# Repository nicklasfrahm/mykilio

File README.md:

# Mykilio

⚠️ **Experimental**: This repository is under active development. Usage in production is not advised, but any kind of feedback is welcome.

Mykilio is the proposal for a new Living Standard with the goal to reimagine infrastructure management and monitoring. It aims to be scalable, lightweight, extensible and secure by applying IoT principles to the datacenter and homelabs.

## 📖 Documentation

The documentation can be found at https://mykil.io.

## 📊 Statistics

Here are some statistics to document my learnings throughout the development process.

| 💣 Fault         | 📈 Occurrences | 😅 Poor excuse                                                                                          |
| ---------------- | -------------- | ------------------------------------------------------------------------------------------------------- |
| Reverse polarity | 1              | Maybe purple and dark grey were not the best choice for +24V and GND.                                   |
| Overvoltage      | 1              | I have shaky hands and why does everything have to be so small?!                                        |
| Short-circuit    | 1              | Next time I am going to solder proper connectors. Promise!                                              |
| Wrong footprint  | 2              | Why do TQFP and DIP have a different pin numbering!?<br/>It was late and SS/TR is very close to RT/CLK. |

## 📄 License

This project is licensed under the terms of the [MIT license](./LICENSE.md).

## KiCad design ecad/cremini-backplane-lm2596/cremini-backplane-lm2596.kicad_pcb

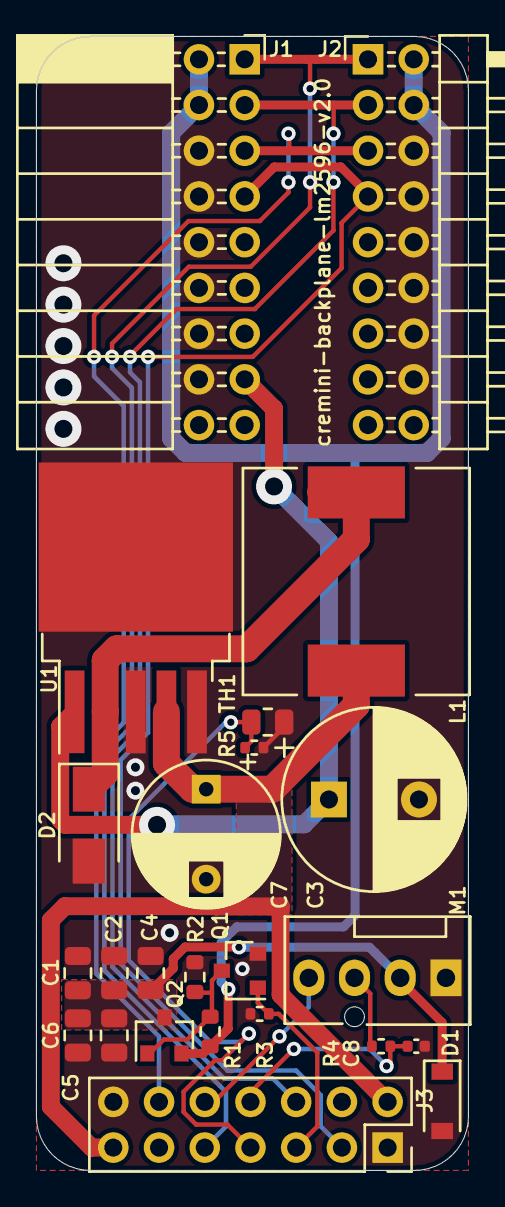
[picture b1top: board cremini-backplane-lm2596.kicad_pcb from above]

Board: 2 copper layers, 24.0 x 63.0 mm, 24 parts (0 on the bottom side), 16 nets.

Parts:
C1, C2, C4, C5, C6: 22uF; C_0805_2012Metric
C3: 680uF; CP_Radial_D10.0mm_P5.00mm
C7: 330uF; CP_Radial_D8.0mm_P5.00mm
C8: 6.8nF; C_0402_1005Metric
D1: B5819W; D_SOD-123
D2: SS54; D_SMA
J1: BUSOUT; PinSocket_2x09_P2.54mm_Horizontal
J2: BUSIN; PinHeader_2x09_P2.54mm_Horizontal
J3: BACKPLANE; PinSocket_2x07_P2.54mm_Vertical
L1: 47uH; L_12x12mm_H8mm
M1: KK 254; FanPinHeader_1x04_P2.54mm_Vertical
Q1: AO3400A; SOT-23
Q2: SI2301CDS-T1-GE3; SOT-23
R1: 1k; R_0603_1608Metric
R2: 1.8k; R_0603_1608Metric
R3, R4, R5: 10k; R_0402_1005Metric
TH1: CMFB103F3950FANT; R_0805_2012Metric
U1: LM2596S-5; TO-263-5_TabPin3

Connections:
5VPSU: C7.1, J3.2, J3.13, L1.2, U1.4
+12V: J1.2, J1.4, J2.2, J2.4, Q2.2, R1.1
FANDCC: J3.5, Q1.1, R3.1
FANFDB: C8.1, J3.8, R4.2
FANPWM: J3.10, M1.4
GND: C1.1, C2.1, C3.2, C4.1, C5.1, C6.1, C7.2, C8.2, D1.2, D2.2, J1.6, J1.8, J1.10, J1.12, J1.14, J1.16, J2.6, J2.8, J2.10, J2.12, J2.14, J2.16, J3.1, J3.14, M1.1, Q1.2, R2.2, R3.2, R5.2, TH1.1, U1.3, U1.5
unnamed: C1.2, C2.2, C4.2, C5.2, C6.2, D1.1, M1.2, Q2.3
unnamed: D2.1, L1.1, U1.2
unnamed: M1.3, R4.1
unnamed: Q1.3, Q2.1, R1.2, R2.1
POWTMP: J3.7, R5.1, TH1.2
SCL: J1.7, J2.7, J3.3
SDA: J1.5, J2.5, J3.12
SRX: J1.3, J2.3, J3.6
STX: J1.1, J2.1, J3.9
VIN: C3.1, J1.9, J1.11, J1.13, J1.15, J2.9, J2.11, J2.13, J2.15, U1.1

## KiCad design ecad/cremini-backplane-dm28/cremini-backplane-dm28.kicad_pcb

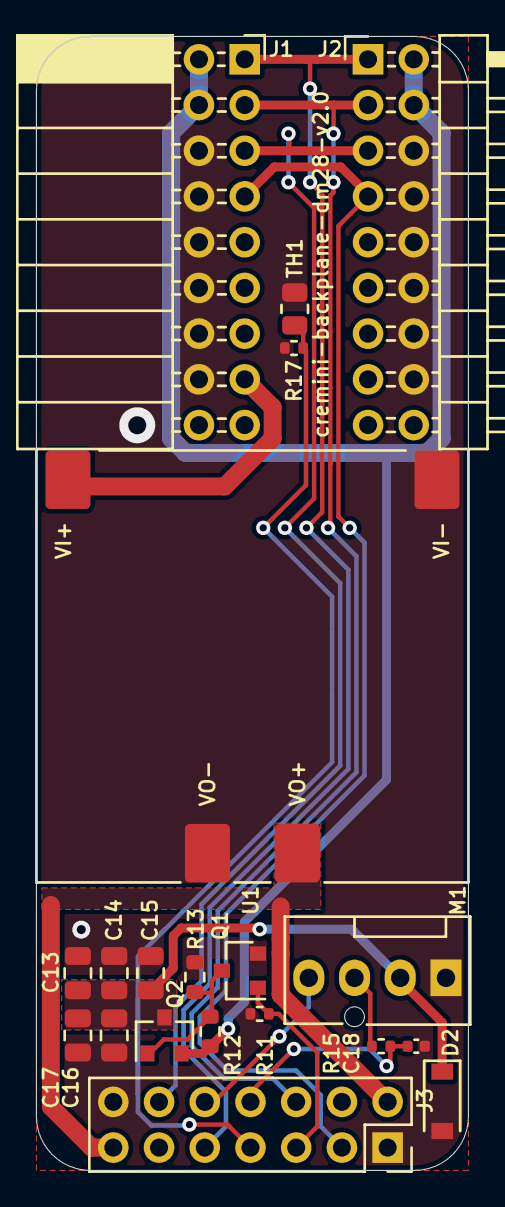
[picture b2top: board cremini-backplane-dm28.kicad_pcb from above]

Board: 2 copper layers, 24.0 x 63.0 mm, 20 parts (0 on the bottom side), 15 nets.

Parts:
C13, C14, C15, C16, C17: 22uF; C_0805_2012Metric
C18: 6.8nF; C_0402_1005Metric
D2: B5819W; D_SOD-123
J1: BUSOUT; PinSocket_2x09_P2.54mm_Horizontal
J2: BUSIN; PinHeader_2x09_P2.54mm_Horizontal
J3: BACKPLANE; PinSocket_2x07_P2.54mm_Vertical
M1: KK 254; FanPinHeader_1x04_P2.54mm_Vertical
Q1: AO3400A; SOT-23
Q2: SI2301CDS-T1-GE3; SOT-23
R11, R15, R17: 10k; R_0402_1005Metric
R12: 1k; R_0603_1608Metric
R13: 1.8k; R_0603_1608Metric
TH1: CMFB103F3950FANT; R_0805_2012Metric
U1: DM28

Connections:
5VPSU: J3.2, J3.13, U1.2
+12V: J1.2, J1.4, J2.2, J2.4, Q2.2, R12.1
FANDCC: J3.5, Q1.1, R11.1
FANFDB: C18.1, J3.8, R15.2
FANPWM: J3.10, M1.4
GND: C13.1, C14.1, C15.1, C16.1, C17.1, C18.2, D2.2, J1.6, J1.8, J1.10, J1.12, J1.14, J1.16, J2.6, J2.8, J2.10, J2.12, J2.14, J2.16, J3.1, J3.14, M1.1, Q1.2, R11.2, R13.2, R17.2, TH1.1, U1.1, U1.3
unnamed: C13.2, C14.2, C15.2, C16.2, C17.2, D2.1, M1.2, Q2.3
unnamed: M1.3, R15.1
unnamed: Q1.3, Q2.1, R12.2, R13.1
POWTMP: J3.7, R17.1, TH1.2
SCL: J1.7, J2.7, J3.3
SDA: J1.5, J2.5, J3.12
SRX: J1.3, J2.3, J3.6
STX: J1.1, J2.1, J3.9
VIN: J1.9, J1.11, J1.13, J1.15, J2.9, J2.11, J2.13, J2.15, U1.4

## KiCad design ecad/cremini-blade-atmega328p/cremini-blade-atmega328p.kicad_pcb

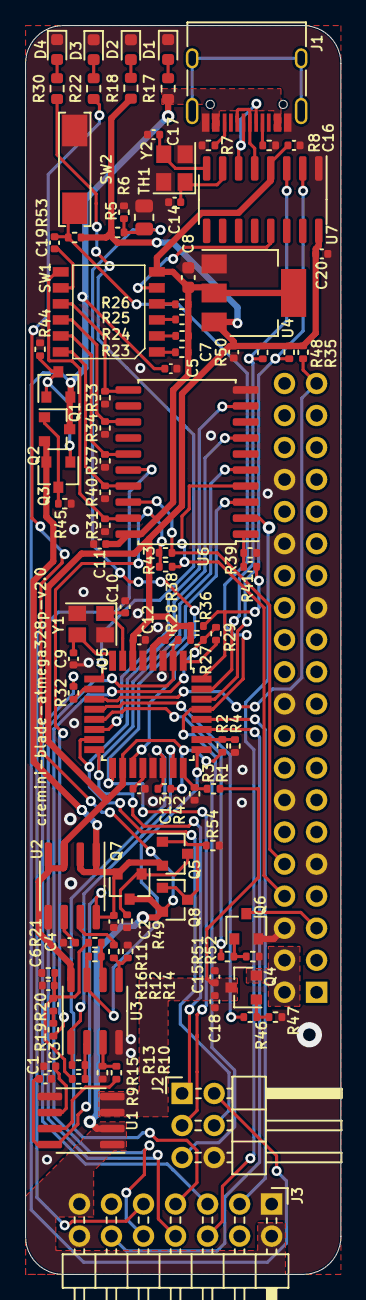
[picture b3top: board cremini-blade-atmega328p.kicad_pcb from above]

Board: 2 copper layers, 25.0 x 99.0 mm, 102 parts (1 on the bottom side), 79 nets.

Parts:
C1, C2, C5, C6, C11, C12, C13, C15, C16, C19, C20: 0.1uF; C_0402_1005Metric
C3, C4: 1nF; C_0402_1005Metric
C7, C18: 10uF; C_0402_1005Metric
C8: 22uF; C_0603_1608Metric
C9, C10, C14, C17: 22pF; C_0402_1005Metric
D1: YELLOW; LED_0603_1608Metric
D2: GREEN; LED_0603_1608Metric
D3, D4: BLUE; LED_0603_1608Metric
J1: USB-C PORT; USB_C_Receptacle_HRO_TYPE-C-31-M-12
J2: ICSP; PinHeader_2x03_P2.54mm_Horizontal
J3: BACKPLANE; PinHeader_2x07_P2.54mm_Horizontal
J4: RASPBERRY PI GPIO; PinSocket_2x20_P2.54mm_Horizontal
Q1, Q3, Q5, Q8: Q_PNP_BEC; SOT-23
Q2, Q7: AO3401A; SOT-23
Q4, Q6: AO3400A; SOT-23
R1, R2: 4.7k; R_0402_1005Metric
R3, R4: 1.2k; R_0402_1005Metric
R5, R42: 27k; R_0402_1005Metric
R6, R9, R10, R11, R12, R27, R35, R39, R47, R52, R53: 10k; R_0402_1005Metric
R7, R8: 5.1k; R_0402_1005Metric
R13, R14, R15, R16, R33, R34, R37, R40, R41, R44, R54: 20k; R_0402_1005Metric
R17: 150; R_0603_1608Metric
R18: 91; R_0603_1608Metric
R19, R20: 24; R_0402_1005Metric
R21: 150; R_0402_1005Metric
R22, R30: 470; R_0603_1608Metric
R23, R24, R25, R26, R28, R29, R31, R32, R36, R38, R43, R46, R48, R50, R51: 1k; R_0402_1005Metric
R45, R49: 100k; R_0402_1005Metric
SW1: SW_DIP_x06; DIP_SW_x06
SW2: RESET; SW_SPST_REED_CT05-XXXX-J1
TH1: CMFB103F3950FANT; R_0805_2012Metric
U1, U2: ACS712ELCTR-20A-T; SOIC-8_3.9x4.9mm_P1.27mm
U3: LM358D; SOIC-8_3.9x4.9mm_P1.27mm
U4: AMS1117-3.3; SOT-223-3_TabPin2
U5: ATMEGA328P-AU; TQFP-32_7x7mm_P0.8mm
U6: 74HC244D; SOIC-20W_7.5x12.8mm_P1.27mm
U7: CH340G; SOIC-16_3.9x9.9mm_P1.27mm
Y1: 16MHz; Crystal_SMD_3225-4Pin_3.2x2.5mm
Y2: 12MHz; Crystal_SMD_3225-4Pin_3.2x2.5mm

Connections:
5VBMC: C1.1, C2.1, Q2.2, Q3.2, Q5.2, Q7.2, U1.8, U2.1, U2.2, U2.8
5VEXT: C5.2, J1.A4, J1.A9, J1.B4, J1.B9, J2.2, Q1.2, Q2.3, R17.1
5VPSU: J3.2, J3.13, Q7.3, Q8.2, R22.1, U1.1, U1.2
5VSBC: C15.1, C18.2, Q4.3, R1.1, U1.3, U1.4
+2V5: C6.1, R9.2, R11.2, R20.2, R21.1
+3V3: C8.1, C11.2, C16.1, R19.1, R23.2, R24.2, R25.2, R26.2, R38.1, R43.2, SW1.6, U4.2, U6.20, U7.4
+5V: C7.2, C12.1, C20.2, R2.1, R5.2, R18.2, R27.2, R28.2, R35.2, R36.2, R42.1, R48.1, R50.1, R53.1, U2.3, U2.4, U3.8, U4.3, U5.4, U5.6, U5.18, U7.16
AMBTMP: R5.1, R6.1, TH1.2, U5.19
ARESET: C19.2, SW1.8
BMCCUR: R16.2, U3.7, U5.25
BMCRX: R48.2, U5.30, U7.2
BMCTX: R50.2, U5.31, U7.3
BMCVOL: R2.2, R4.1, U5.26
CIPO: J2.1, U5.16, U6.5
COPI: J2.4, U5.15, U6.7
D+: J1.A6, J1.B6, U7.5
D-: J1.A7, J1.B7, U7.6
DTR: SW1.5, U7.13
FANDCC: J3.5, R32.1
FANFDB: J3.8, R28.1, U5.2
FANPWM: J3.10, R27.1, R29.1
GND: C1.2, C2.2, C3.2, C4.2, C5.1, C6.2, C7.1, C8.2, C9.2, C10.2, C11.1, C12.2, C13.2, C14.1, C15.2, C16.2, C17.2, C18.1, C20.1, D1.1, D2.1, D3.1, D4.1, J1.A1, J1.A12, J1.B1, J1.B12, J2.6, J3.1, J3.14, J4.6, J4.9, J4.14, J4.20, J4.25, J4.30, J4.34, Q6.2, R3.2, R4.2, R6.2, R7.2, R8.2, R13.2, R14.2, R21.2, R31.1, R33.2, R34.2, R37.2, R40.2, R41.2, R44.2, R45.2, R47.1, R49.2, R52.2, R54.2, SW2.2, TH1.1, U1.5, U2.5, U3.4, U4.1, U5.3, U5.5, U5.21, U6.10, U7.1, Y1.2, Y1.4, Y2.2, Y2.4
unnamed: C3.1, U1.6
unnamed: C4.1, U2.6
unnamed: C9.1, U5.8, Y1.3
unnamed: C10.1, U5.7, Y1.1
unnamed: C13.1, U5.20
unnamed: C14.2, U7.7, Y2.1
unnamed: C17.1, U7.8, Y2.3
unnamed: D1.2, R17.2
unnamed: D2.2, R18.1
unnamed: D3.2, R22.2
unnamed: D4.2, R30.2
unnamed: J1.A5, R8.1
unnamed: J1.B5, R7.1
unnamed: J4.2, J4.4, Q4.2
unnamed: J4.5, Q6.3
unnamed: Q1.1, Q1.3, Q3.1, R44.1
unnamed: Q2.1, Q3.3, R45.1
unnamed: Q4.1, R46.2, R47.2
unnamed: Q5.1, Q8.1, Q8.3, R54.1
unnamed: Q5.3, Q7.1, R49.1
unnamed: Q6.1, R51.1, R52.1
unnamed: R10.1, U1.7
unnamed: R10.2, R13.1, U3.3
unnamed: R11.1, R16.1, U3.6
unnamed: R12.1, U2.7
unnamed: R12.2, R14.1, U3.5
unnamed: R9.1, R15.1, U3.2
unnamed: R19.2, R20.1
unnamed: R23.1, SW1.1
unnamed: R24.1, SW1.2
unnamed: R25.1, SW1.3
unnamed: R26.1, SW1.4
unnamed: R29.2, U5.1
unnamed: R30.1, U5.9
unnamed: R31.2, SW1.7, U6.19
unnamed: R32.2, U5.10
unnamed: R33.1, SW1.9, U6.11
unnamed: R34.1, SW1.10, U6.13
unnamed: R37.1, SW1.11, U6.15
unnamed: R39.1, R41.1, U6.1
unnamed: R40.1, SW1.12, U6.17
PB2: U5.14, U6.9
POWTMP: J3.7, R42.2, U5.22
RESET: C19.1, J2.5, R53.2, SW2.1, U5.29
SBCCON: J4.39, R35.1, U5.11
SBCCUR: R15.2, U3.1, U5.23
SBCPON: R46.1, U5.12
SBCRX: J4.10, R43.1, U6.18
SBCSON: R51.2, U5.13
SBCTX: J4.8, R38.2, U6.4
SBCVOL: R1.2, R3.1, U5.24
SCK: J2.3, U5.17, U6.3
SCL: J3.3, U5.28
SDA: J3.12, U5.27
SEN: R36.1, R39.2, U5.32
SRX: J3.6, U6.2
STX: J3.9, U6.16

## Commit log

2021-05-02 Initialize repository
2021-05-03 Fix CNAME file
2021-05-03 Organize docs and start documenting the management interface
2021-05-04 Define mycelium state enumerations
2021-05-04 Organize management bus interface by data categories
2021-05-05 Add missing status register for PSU state
2021-05-05 Finish definition of management bus interface
2021-05-06 Adjust documentation layout
2021-05-06 Add action registers and more detailed description for specification registers
2021-05-06 Document DUTSET register
2021-05-06 Create basic header files for management bus interface
2021-05-07 Organize Makefile
2021-05-07 Organize repository
2021-05-07 Implement management bus interface on blade BMC
2021-05-07 Start auto-discovery implementation
2021-05-08 Implement TWI device discovery and remote LED toggling
2021-05-09 Organize controller TWI implementation
2021-05-09 Document data framing
2021-05-10 Fix broken image due to Git LFS
2021-05-11 Implement USART via file streams
2021-05-11 Change LED for blade
2021-05-11 Configure BAUD at runtime
2021-05-11 Implement configurable TWI address
2021-05-15 Configure SSH for deployment infrastructure
2021-05-15 Fix SSH action configuration
2021-05-15 Perform sanity check of GitHub action
2021-05-15 Fix variable reference
2021-05-15 Deploy k3s
2021-05-15 Test own GitHub action
2021-05-16 Rename file to kubeconfig
2021-05-16 Create secret from kubeconfig
2021-05-17 Organize ECAD files
2021-05-17 Fix footprint 3D models
2021-05-17 Align pin numbering of backplane and blade
2021-05-17 Debug GitHub actions
2021-05-17 Test file secret action
2021-05-17 Fix file secret action configuration
2021-05-17 Fix deployment of k3s infrastructure component
2021-05-17 Remove default Traefik installation
2021-05-17 Enable SELinux
2021-05-17 Fix kubeconfig mode
2021-05-17 Fix installation script
2021-05-17 Fix k3s installation
2021-05-18 Install kube toolchain
2021-05-18 Install traefik and cert-manager
2021-05-18 Fix deployment of cert-manager and traefik
2021-05-18 Fix infrastructure workflow trigger for cert-manager and traefik
2021-05-18 Fix file names in step files
2021-05-18 Fix invalid workflow configuration
2021-05-18 Add infrastructure status badge
2021-05-18 Adjust ingress configuration to accomodate missing hairpin NAT
2021-05-18 Reconfigure infrastructure environment
2021-05-19 Add powerful makefile for Golang controllers
2021-05-19 Add statistics and emojis
2021-05-19 AFix grammar
2021-05-19 Update documentation with drafted content
2021-05-19 Fix documentation frontpage
2021-05-19 Adjust emoji
2021-05-20 Set up alpha environment
2021-05-20 Canonicalize file naming for deployment configurations
2021-05-20 Use defaults in workflow
2021-05-20 Fix broken infrastructure workflow
2021-05-20 Provision TLS certificate
2021-05-20 Fix TLS certificate job gate
2021-05-20 Disable redirect for all HTTP request to allow ACME
2021-05-20 Configure EMQX deployment
2021-05-20 Adjust loaded plugins configuration
2021-05-20 Use values.yml to configure loaded plugins
2021-05-20 Configure the signals SBCCON, SBCPON and SBCSON
2021-05-20 Verify infrastructure status after deployment
2021-05-20 Remove ping job
2021-05-20 Add test job to infrastructure workflow
2021-05-21 Set up container build for first controller
2021-05-21 Fix job name
2021-05-21 Fix controller workflow
2021-05-21 Fix matrix reference
2021-05-21 Add Dockerfile
2021-05-21 Add go.* files
2021-05-21 Fix Dockerfile
2021-05-21 Fix build-args
2021-05-21 Fix controller reference
2021-05-21 Use canonical controller implementation
2021-05-21 Add controller workflow status badge
2021-05-21 Remove unnecessary line in Makefile
2021-05-21 Trigger alpha deployment every time new images are available
2021-05-21 Update documentation
2021-05-21 Organize deployment folder
2021-05-21 Attempt to deploy postgresql
2021-05-21 Install kubeconfig for uzser
2021-05-21 Fix file permission for kubeconfig
2021-05-21 Shorten database name
2021-05-21 Create first draft for controller helm chart
2021-05-21 Fix security context
2021-05-21 Lock ingress version
2021-05-21 Force string values in environment variables
2021-05-21 Quote all strings
2021-05-21 Fix volume permissions
2021-05-21 Fix init container
2021-05-21 Adjust permissions by creating volume copy
2021-05-21 Remove invalid property for secret volume
2021-05-21 Log failed requests
2021-05-21 Fix ingress path type
2021-05-22 Force pod recreation during rollout
2021-05-22 Force pod recreation
2021-05-22 Always pull images due to main tag
2021-05-22 Enable TLS for MQTTS and HTTPS port
2021-05-22 Make probes less aggressive
2021-05-22 Rewrite path
2021-05-22 Reference middleware in ingress definition
2021-05-22 Fix service root
2021-05-22 Fix path rewriting and speed up deployment rollout
2021-05-22 Install all controllers
2021-05-22 Fix trigger for container updates
2021-05-22 Fix EMQ X auth plugin config
2021-05-22 Disable ACL plugin and fix content type header
2021-06-02 Configure Ethernet on WT32-ETH0
2021-06-03 Organize ethernet and IP code
2021-06-03 Fix netmask prefix function
2021-06-03 Permit full remote control over blade
2021-06-03 Set up MQTT via TLS client
2021-06-09 Move authenticatiton webhook to core.mykil.io
2021-06-09 Use absolute default migration path
2021-06-09 Disable DB connection temporarily
2021-06-10 Fix database migration in controller
2021-06-10 Fix certificate directory environment variable
2021-06-10 Seperate build and deployment of documentation
2021-06-10 Configure build step as dependency of deployment step
2021-06-10 Configure deployment URL
2021-06-10 Hardcode documentation domain
2021-06-10 Automatically update EMQ X configuration on upgrades
2021-06-11 Rename documentation environment
2021-06-14 Move ICSP header by extending PCB
2021-06-15 Update blade PCB step file
2021-06-15 Fix CI pipeline by add correct job for blade
2021-06-19 Document Google Drive folder
2021-06-19 Document CJS1 simulations
2021-06-20 Fix backpower protection of cremini v2
2021-06-20 Reroute PCB for backpower protection circuit
2021-06-20 Fix silk screen and export latest STEP file
2021-06-24 Route LM2596 backplane
2021-06-24 Update schematic of blade with reserved pins
2021-06-24 Generate STEP file for LM2596 backplane
2021-06-25 Sync current state to GitHub
2021-06-27 Add Pi4 assembly with heatsinks
2021-06-27 Remove cremini STEP file
2021-06-27 Add simulations to GitHub repository
2021-06-27 Create FreeCAD file for backplane
2021-06-27 Reduce size of FreeCAD file
2021-06-27 Reduce size of CAD files
2021-06-27 Add blade to assembly
2021-06-27 Assemble single blade
2021-06-27 Update assembly
2021-06-27 Document conventions for FreeCAD files
2021-06-27 Rebrand DM28 backplane
2021-06-27 Render DM28 backplane
2021-06-27 ci(#21): Improve release and distribution pipeline
2021-06-27 ci(#21): add zip step before upload
2021-06-27 ci(#21): fix wrong zip upload
2021-06-27 ci(#21): fix root directory of zip
2021-06-27 ci(#21): fix release zip location
2021-06-27 Create FreeCAD assembly (#24)
    * Add Pi4 assembly with heatsinks
    * Remove cremini STEP file
    * Add simulations to GitHub repository
    * Create FreeCAD file for backplane
    * Reduce size of FreeCAD file
    * Reduce size of CAD files
2021-07-13 Read data from ADC
2021-08-28 Deploy to GitHub pages
2021-09-12 Measure fan speed
2021-09-17 Measure fan frequency
2021-10-27 Bump nltk from 3.6.2 to 3.6.5
    Bumps [nltk](https://github.com/nltk/nltk) from 3.6.2 to 3.6.5.
    - [Release notes](https://github.com/nltk/nltk/releases)
    - [Changelog](https://github.com/nltk/nltk/blob/develop/ChangeLog)
    - [Commits](https://github.com/nltk/nltk/compare/3.6.2...3.6.5)
    ---
    updated-dependencies:
2021-10-27 Bump mkdocs from 1.1.2 to 1.2.3
    Bumps [mkdocs](https://github.com/mkdocs/mkdocs) from 1.1.2 to 1.2.3.
    - [Release notes](https://github.com/mkdocs/mkdocs/releases)
    - [Commits](https://github.com/mkdocs/mkdocs/compare/1.1.2...1.2.3)
    ---
    updated-dependencies:
    - dependency-name: mkdocs
2022-05-17 Bump nltk from 3.6.5 to 3.6.6
    Bumps [nltk](https://github.com/nltk/nltk) from 3.6.5 to 3.6.6.
    - [Release notes](https://github.com/nltk/nltk/releases)
    - [Changelog](https://github.com/nltk/nltk/blob/develop/ChangeLog)
    - [Commits](https://github.com/nltk/nltk/compare/3.6.5...3.6.6)
    ---
    updated-dependencies:
2022-09-30 Bump joblib from 1.0.1 to 1.2.0
    Bumps [joblib](https://github.com/joblib/joblib) from 1.0.1 to 1.2.0.
    - [Release notes](https://github.com/joblib/joblib/releases)
    - [Changelog](https://github.com/joblib/joblib/blob/master/CHANGES.rst)
    - [Commits](https://github.com/joblib/joblib/compare/1.0.1...1.2.0)
    ---
    updated-dependencies:
2023-03-07 Bump future from 0.18.2 to 0.18.3
    Bumps [future](https://github.com/PythonCharmers/python-future) from 0.18.2 to 0.18.3.
    - [Release notes](https://github.com/PythonCharmers/python-future/releases)
    - [Changelog](https://github.com/PythonCharmers/python-future/blob/master/docs/changelog.rst)
    - [Commits](https://github.com/PythonCharmers/python-future/compare/v0.18.2...v0.18.3)
    ---
    updated-dependencies:
2023-03-07 Bump azure/setup-kubectl from 1 to 3 in /.github/workflows
    Bumps [azure/setup-kubectl](https://github.com/azure/setup-kubectl) from 1 to 3.
    - [Release notes](https://github.com/azure/setup-kubectl/releases)
    - [Commits](https://github.com/azure/setup-kubectl/compare/v1...v3)
    ---
    updated-dependencies:
    - dependency-name: azure/setup-kubectl
2023-05-15 Bump pymdown-extensions from 8.1.1 to 10.0
    Bumps [pymdown-extensions](https://github.com/facelessuser/pymdown-extensions) from 8.1.1 to 10.0.
    - [Release notes](https://github.com/facelessuser/pymdown-extensions/releases)
    - [Commits](https://github.com/facelessuser/pymdown-extensions/compare/8.1.1...10.0)
    ---
    updated-dependencies:
    - dependency-name: pymdown-extensions
2023-05-25 Bump tornado from 6.1 to 6.3.2
    Bumps [tornado](https://github.com/tornadoweb/tornado) from 6.1 to 6.3.2.
    - [Changelog](https://github.com/tornadoweb/tornado/blob/master/docs/releases.rst)
    - [Commits](https://github.com/tornadoweb/tornado/compare/v6.1.0...v6.3.2)
    ---
    updated-dependencies:
    - dependency-name: tornado
